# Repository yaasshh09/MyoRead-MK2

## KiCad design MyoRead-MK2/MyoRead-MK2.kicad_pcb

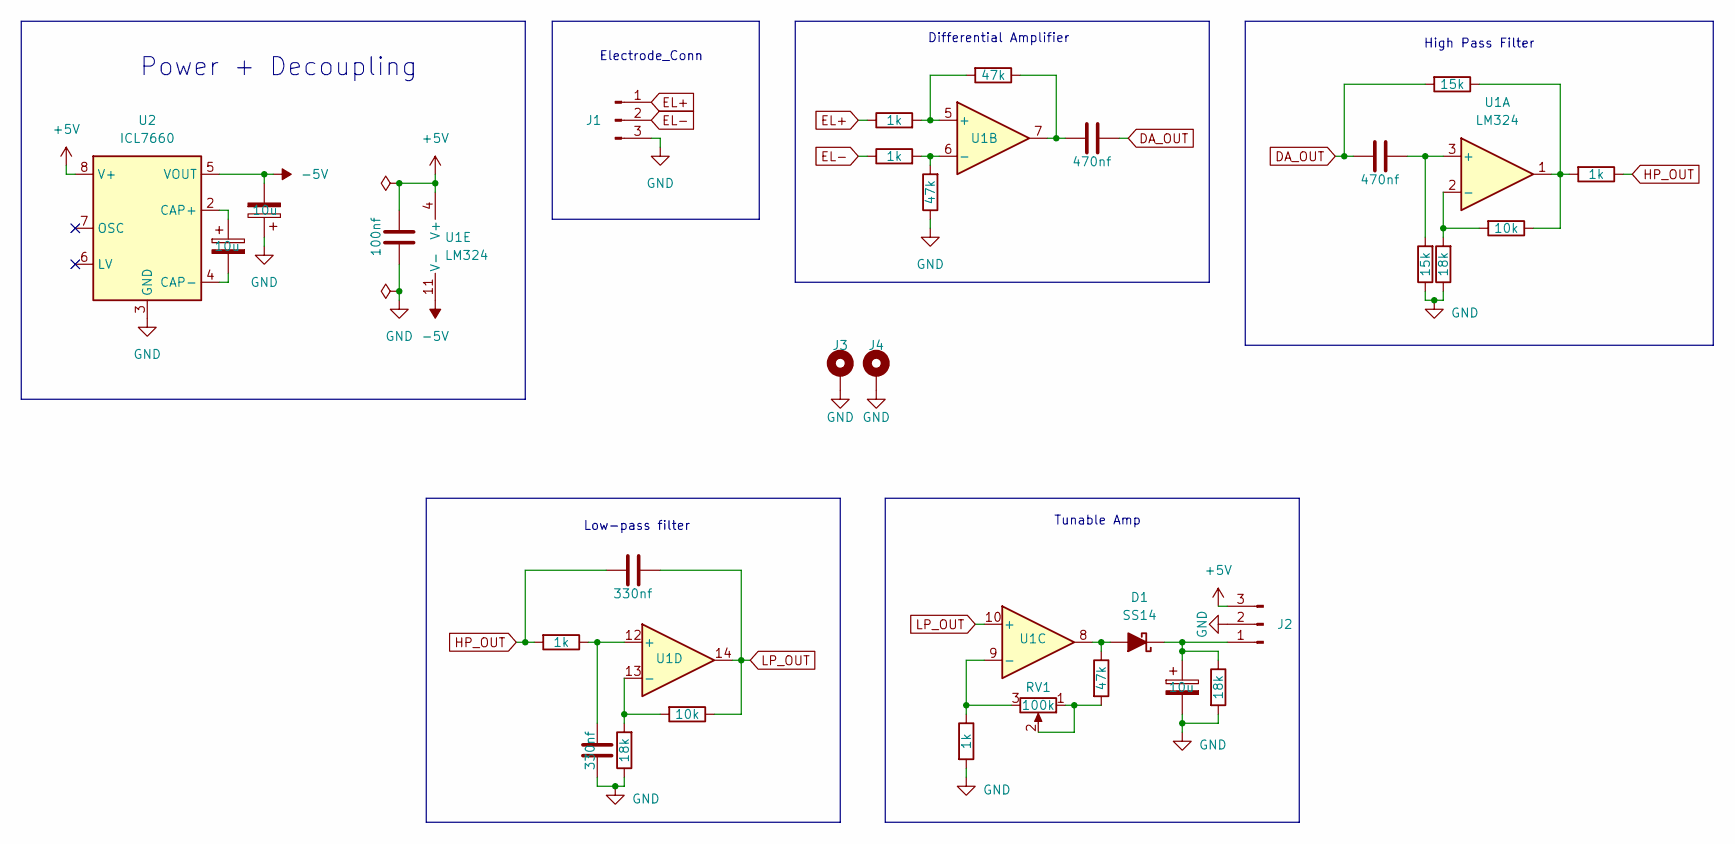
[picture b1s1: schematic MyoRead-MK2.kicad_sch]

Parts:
C1: 100nf; C_0805_2012Metric
C2, C3: 470nf; C_0805_2012Metric
C4, C5, C8: 10u; CP_Elec_6.3x4.5
C6, C7: 330nf; C_0805_2012Metric
D1: SS14; D_SMA
J1: Electrode; PinHeader_1x03_P2.54mm_Vertical
J2: Conn_01x03_Pin; PinHeader_1x03_P2.54mm_Vertical
J3, J4: Mounting_hole; MountingHole_2.2mm_M2_DIN965_Pad
R1, R2, R9, R15, R16: 1k; R_0805_2012Metric
R3, R4, R17: 47k; R_0805_2012Metric
R5, R8: 15k; R_0805_2012Metric
R6, R13: 10k; R_0805_2012Metric
R7, R11, R18: 18k; R_0805_2012Metric
RV1: 100k; Potentiometer_Bourns_TC33X_Vertical
U1: LM324; SOIC-14_3.9x8.7mm_P1.27mm
U2: ICL7660; SOP-8_3.76x4.96mm_P1.27mm

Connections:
+5V: C1.1, J2.3, U1.4 (V+), U2.8 (V+)
-5V: C5.2, U1.11 (V-), U2.5 (VOUT)
DA_OUT: C2.2, C3.1, R5.2
EL+: J1.1, R1.1
EL-: J1.2, R2.1
GND: C1.2, C5.1, C7.1, C8.2, J1.3, J2.2, J3.1 (1_1), J4.1 (1_1), R3.1, R7.1, R8.1, R11.1, R16.2, R18.2, U2.3 (GND)
HP_OUT: C6.1, R9.1, R15.2
unnamed: C2.1, R4.1, U1.7
unnamed: D1.2 (A), R17.1, U1.8
unnamed: C8.1, D1.1 (K), J2.1, R18.1
unnamed: R5.1, R6.1, R9.2, U1.1
unnamed: R17.2, RV1.1, RV1.2
unnamed: C3.2, R8.2, U1.3 (+)
unnamed: R6.2, R7.2, U1.2 (-)
unnamed: R1.2, R4.2, U1.5 (+)
unnamed: R2.2, R3.2, U1.6 (-)
unnamed: C6.2, R13.1, U1.10 (+), U1.14
unnamed: R16.1, RV1.3, U1.9 (-)
unnamed: C7.2, R15.1, U1.12 (+)
unnamed: R11.2, R13.2, U1.13 (-)
unnamed: C4.1, U2.2 (CAP+)
unnamed: C4.2, U2.4 (CAP-)

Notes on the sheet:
Differential Amplifier
Low-pass filter
High Pass Filter
Tunable Amp
Power + Decoupling
Electrode_Conn

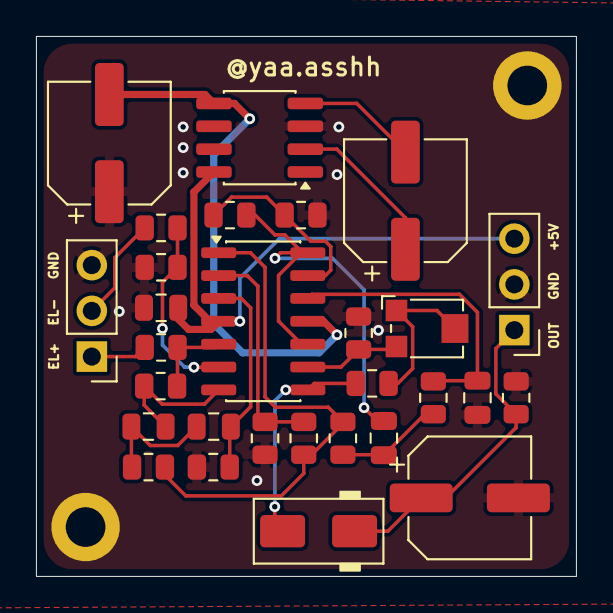
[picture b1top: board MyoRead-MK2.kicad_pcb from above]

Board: 2 copper layers, 30.0 x 30.0 mm, 31 parts (0 on the bottom side), 22 nets.

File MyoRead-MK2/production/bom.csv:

Designator,Footprint,Quantity,Value,LCSC Part #
C1,0805,1,100nf,
"C2, C3",0805,2,470nf,
"C4, C5, C8",CP_Elec_6.3x4.5,3,10u,
"C6, C7",0805,2,330nf,
D1,D_SMA,1,SS14,
J1,PinHeader_1x03_P2.54mm_Vertical,1,Electrode,
J2,PinHeader_1x03_P2.54mm_Vertical,1,Conn_01x03_Pin,
"J3, J4",MountingHole_2.2mm_M2_DIN965_Pad,2,Mounting_hole,
"R1, R15, R16, R2, R9",0805,5,1k,
"R11, R18, R7",0805,3,18k,
"R13, R6",0805,2,10k,
"R17, R3, R4",0805,3,47k,
"R5, R8",0805,2,15k,
RV1,Potentiometer_Bourns_TC33X_Vertical,1,100k,
U1,SOIC-14_3.9x8.7mm_P1.27mm,1,LM324,
U2,SOP-8_3.76x4.96mm_P1.27mm,1,ICL7660,
